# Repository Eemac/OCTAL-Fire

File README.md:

# OCTAL-Fire
The largest collegiate-built drone in the world!
[OCTAL Website!](https://octalfire.com/)

## What/Why is this project?
OCTAL is engineered to respond to wildfires faster--and safer--than humans can. Satellites can already detect hotspots with a resolution of ~500ft. Our system will autonomously deploy to the detected hotspot, perform an analysis with 6 visible and infrared-spectrum cameras, and release retardant before the fire has time to get large, saving wildlife, property, and human lives. With four 66Ah, 60V solid-state LiPo battery packs, a 120kg payload, and a projected 40-minute flight time, OCTAL is built smart, tough, and versatile.

## Commands for power-up on the CANable:
- sudo slcand -f -o -s6 -S 115200 -t hw /dev/ttyACMX can0
- sudo ip link set can0 up
- candump can0
- cansniffer -t 0 can0 (-t 0 will display all messages)
- cansend can0

## CANable Web Flasher:
[Link Here](https://canable.io/updater/canable2.html)

## Directory Structure:
### Root

| Path | Description |
|---|---|
| `Firmware/` | Embedded firmware for flight systems, BMS, charger, and CAN communication. |
| `Hardware/` | KiCad PCB designs, fabrication outputs, and mechanical files. |
| `libraries/` | Shared KiCad symbols, footprints, and 3D models. |
| `Software (Sensing)/` | Placeholder for sensing-side software. |
| `Software (Base Station)/` | Placeholder for base station software. |
| `README.md` | Main project overview. |

---

### Firmware/
Main embedded software tree.

| Path | Description |
|---|---|
| `Core/` | Main flight controller firmware. |
| `BMS/` | Battery Management System firmware. |
| `Charger/` | Charger controller firmware. |
| `can_api/` | Python CAN code-generation tools. |
| `libraries/` | Embedded driver libraries. |
| `can_lib.dbc` | CAN database definitions. |
| `x11.dbc` | Additional CAN message definitions. |
| `requirements.txt` | Python dependencies. |
| `run.sh` | Build script. for CAN message functions |

### Firmware/can_api/

Python tooling for generating CAN interfaces.

| File | Description |
|---|---|
| `c_generator.py` | Generates C CAN interface code. |
| `dbc_generator.py` | Generates DBC files. |
| `yaml_handler.py` | Parses YAML definitions. |
| `utils.py` | Shared helper functions. |
| `tests/` | Unit tests for generators. |
| `files/c_templates/` | Templates for generated C code. |

---

### Hardware/

PCB and electrical hardware designs.

| PCB / Project | Description |
|---|---|
| `Core/flight-core` | Main flight controller and avionics motherboard integrating STM32 control, CAN routing, power conversion, Cube interface logic, and system interconnects. |
| `BMS/` | Battery Management System board handling cell monitoring, balancing, thermistor sensing, fan control, and high-voltage battery telemetry. |
| `Power Board/` | High-current power distribution board for routing battery power to vehicle subsystems and monitoring thermal/load conditions. |
| `PowerFet/` | High-side MOSFET switching board for controllable power distribution and subsystem shutdown protection. |
| `Charger/` | Dedicated battery charger controller board with onboard regulators, USB-C input handling, and programmable charge control circuitry. |
| `GroundRing/` | Ground-distribution PCB intended to centralize system grounding and reduce high-current return path issues. |
| `Cube-Flipper/` | Adapter/interface board for Cube flight controller mounting or signal rerouting. |
| `Power Board/Thermistors/` | Small thermistor sensing daughterboard used for distributed temperature monitoring. |
| `Coaster/` | Small auxiliary/demo PCB project included in the repository. |
---

### libraries/

Shared KiCad libraries.

| Path | Description |
|---|---|
| `3DModels/` | STEP/STP component models. |
| `OlinBAD.pretty/` | Custom PCB footprints. |
| `parts/` | Symbols, footprints, datasheets, and docs. |
| `OlinBAD.kicad_sym` | KiCad symbol library. |

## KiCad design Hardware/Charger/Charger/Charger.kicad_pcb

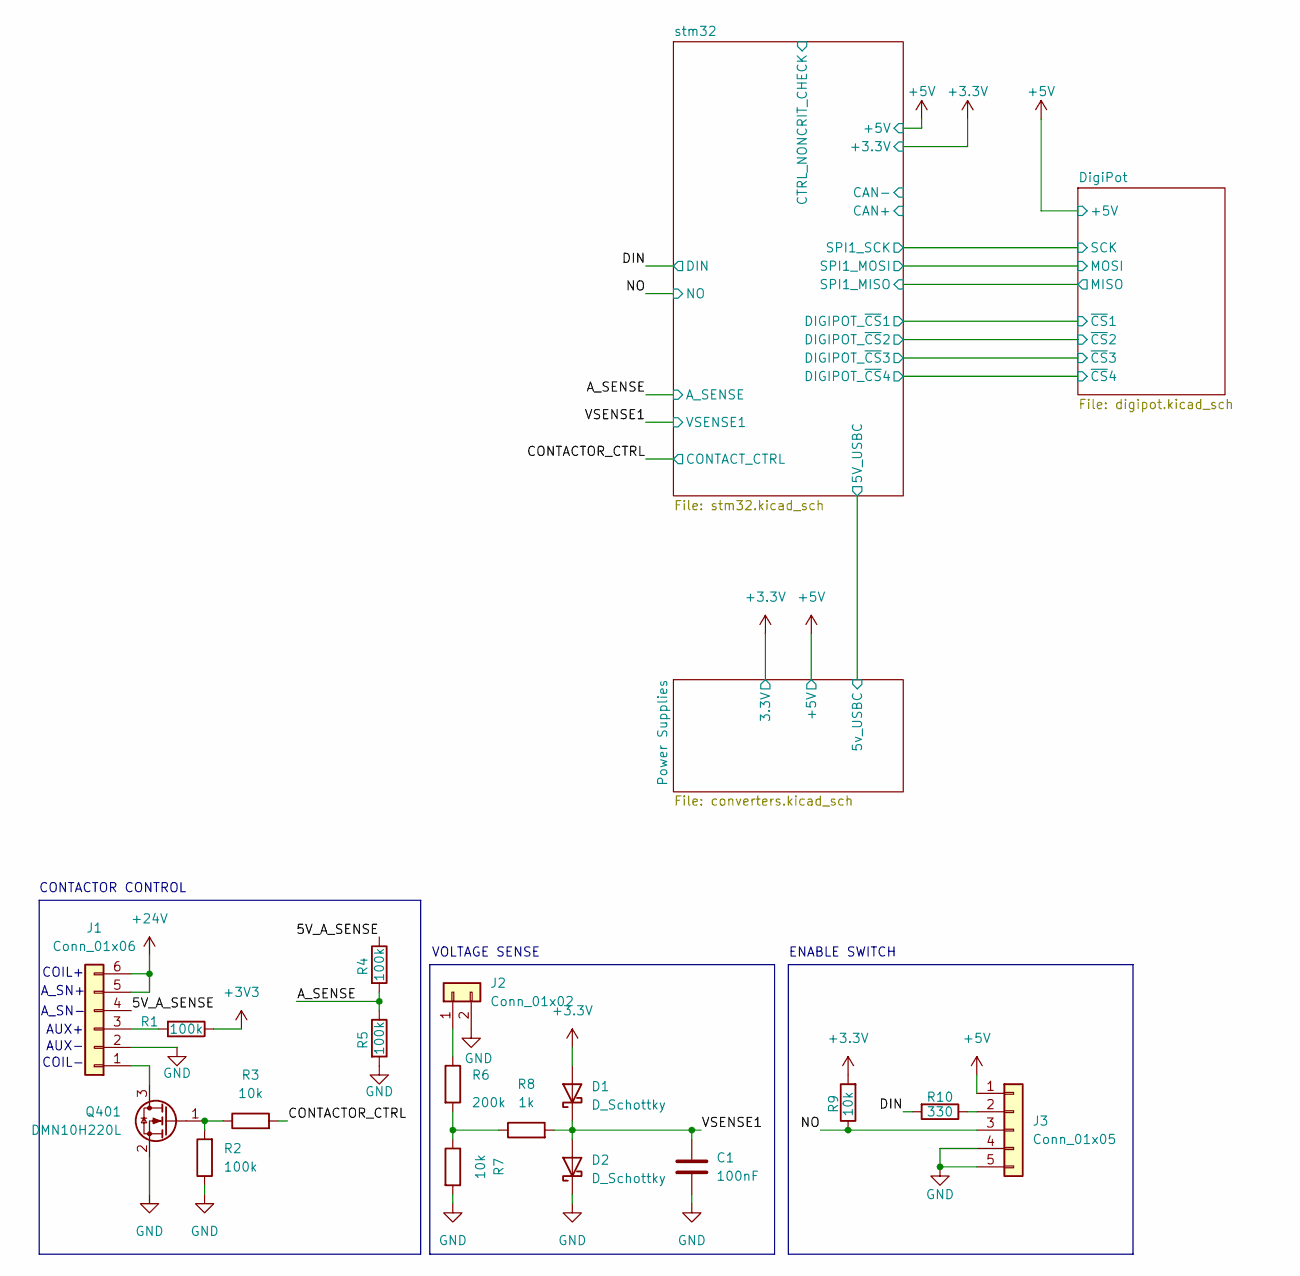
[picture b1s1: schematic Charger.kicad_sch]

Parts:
C1: 100nF; C_0603_1608Metric
D1, D2: D_Schottky; D_0201_0603Metric
J1: Conn_01x06; Molex_Micro-Fit_3.0_43650-0600_1x06_P3.00mm_Horizontal
J2: Conn_01x02; Molex_Micro-Fit_3.0_43650-0200_1x02_P3.00mm_Horizontal
J3: Conn_01x05; Molex_Micro-Fit_3.0_43650-0500_1x05_P3.00mm_Horizontal
Q401: DMN10H220L; SOT-23
R1, R2, R4, R5: 100k; R_0603_1608Metric
R3, R7, R9: 10k; R_0603_1608Metric
R6: 200k; R_0603_1608Metric
R8: 1k; R_0603_1608Metric
R10: 330; R_0603_1608Metric

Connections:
+3.3V: D1.2 (A), R9.2; also elsewhere on the board
+3V3: R1.1
+5V: J3.1; also elsewhere on the board
+24V: J1.5, J1.6; also elsewhere on the board
/5V_A_SENSE: J1.4, R4.1
/A_SENSE: R4.2, R5.1; also elsewhere on the board
/CONTACTOR_CTRL: R3.2; also elsewhere on the board
/DIN: R10.2; also elsewhere on the board
/NO: J3.3, R9.1; also elsewhere on the board
/VSENSE1: C1.1, D1.1 (K), D2.2 (A), R8.2; also elsewhere on the board
GND: C1.2, D2.1 (K), J1.2, J2.2, J3.4, J3.5, Q401.2 (S), R2.1, R5.2, R7.2; also elsewhere on the board
unnamed: J1.1, Q401.3 (D)
unnamed: J1.3, R1.2
unnamed: J2.1, R6.1
unnamed: J3.2, R10.1
unnamed: Q401.1 (G), R2.2, R3.1
unnamed: R6.2, R7.1, R8.1

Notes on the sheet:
COIL+
CONTACTOR CONTROL
COIL-
A_SN+
AUX-
A_SN-
AUX+
VOLTAGE SENSE
ENABLE SWITCH

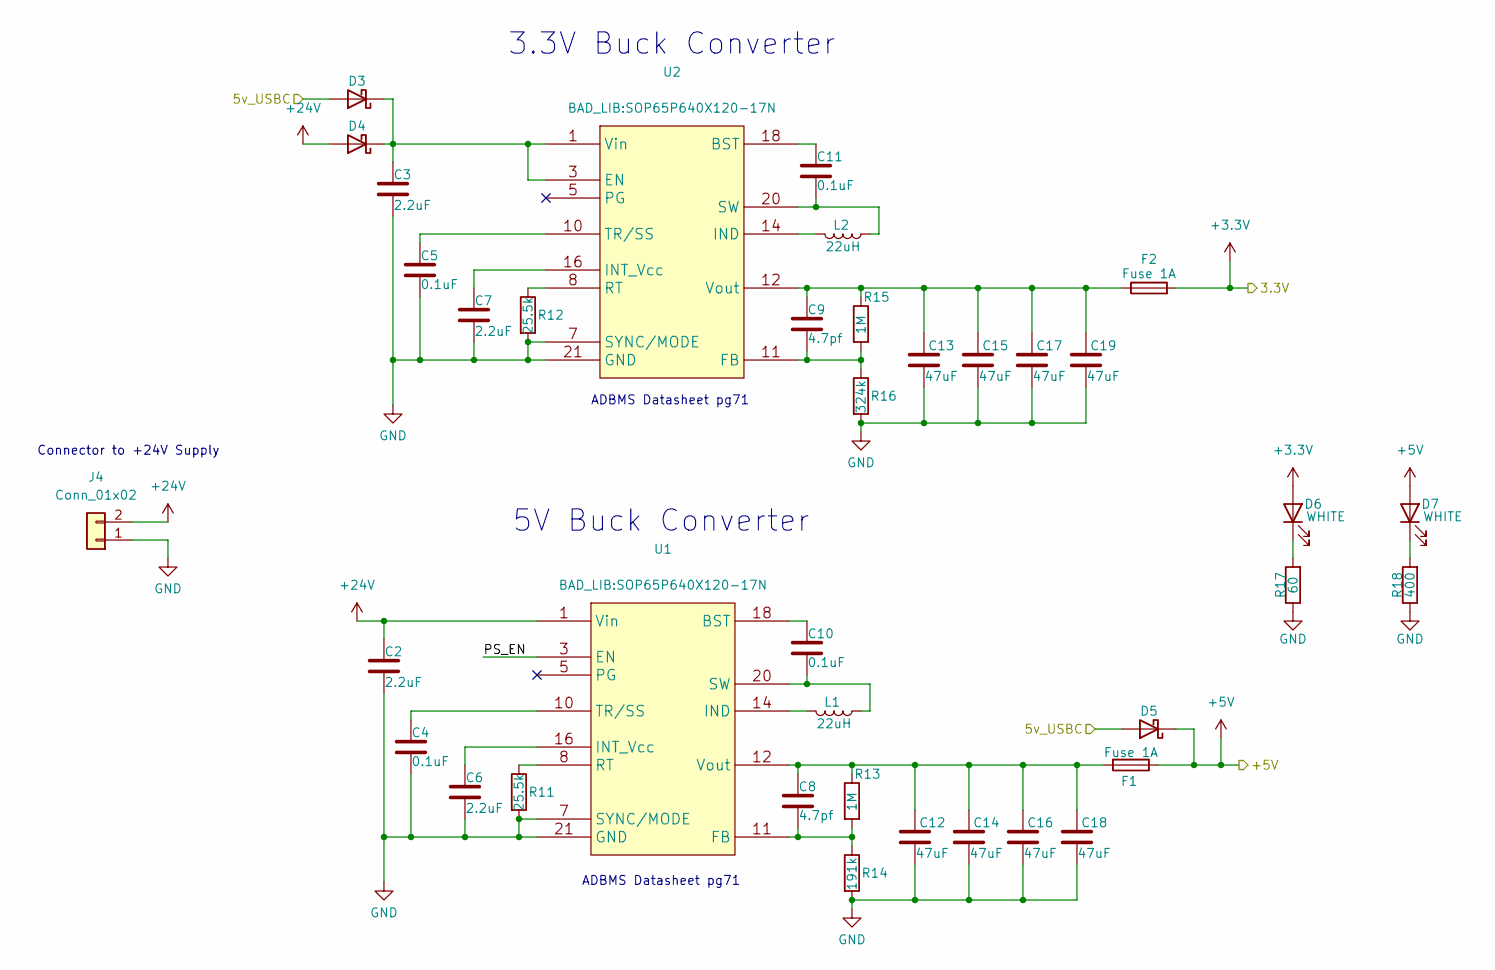
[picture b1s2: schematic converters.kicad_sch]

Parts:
C2, C3: 2.2uF; C_0805_2012Metric
C4, C5, C10, C11: 0.1uF; C_0603_1608Metric
C6, C7: 2.2uF; C_0603_1608Metric
C8, C9: 4.7pf; C_0603_1608Metric
C12, C13, C14, C15, C16, C17, C18, C19: 47uF; C_1206_3216Metric
D3, D4, D5: 60V 3A; DO-220AA_SS2PH10-M3&slash_84A_VIS; MPN V3P6L-M3/H
D6, D7: WHITE; LED_0805_2012Metric
F1, F2: Fuse 1A; Fuse_1206_3216Metric
J4: Conn_01x02; Molex_Micro-Fit_3.0_43650-0200_1x02_P3.00mm_Horizontal
L1, L2: 22uH; L_12x12mm_H4.5mm
R11, R12: 25.5k; R_0603_1608Metric
R13, R15: 1M; R_0603_1608Metric
R14: 191k; R_0603_1608Metric
R16: 324k; R_0603_1608Metric
R17: 60; R_0603_1608Metric
R18: 400; R_0603_1608Metric
U1, U2: SOP65P640X120-17N

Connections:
+3.3V: D6.2 (A), F2.2; also elsewhere on the board
+5V: D5.1 (K), D7.2 (A), F1.1; also elsewhere on the board
+24V: C2.1, D4.2 (A), J4.2, U1.1 (Vin); also elsewhere on the board
/Power Supplies/5v_USBC: D3.2 (A), D5.2 (A); also elsewhere on the board
/Power Supplies/PS_EN: U1.3 (EN)
GND: C2.2, C3.2, C4.2, C5.2, C6.2, C7.2, C12.2, C13.2, C14.2, C15.2, C16.2, C17.2, C18.2, C19.2, J4.1, R11.2, R12.2, R14.2, R16.2, R17.1, R18.1, U1.7 (SYNC/MODE), U1.21 (GND), U2.7 (SYNC/MODE), U2.21 (GND); also elsewhere on the board
unnamed: C3.1, D3.1 (K), D4.1 (K), U2.1 (Vin), U2.3 (EN)
unnamed: D6.1 (K), R17.2
unnamed: D7.1 (K), R18.2
unnamed: C10.1, U1.18 (BST)
unnamed: C8.2, R13.2, R14.1, U1.11 (FB)
unnamed: L1.2, U1.14 (IND)
unnamed: C6.1, U1.16 (INT_Vcc)
unnamed: R11.1, U1.8 (RT)
unnamed: C10.2, L1.1, U1.20 (SW)
unnamed: C4.1, U1.10 (TR/SS)
unnamed: C8.1, C12.1, C14.1, C16.1, C18.1, F1.2, R13.1, U1.12 (Vout)
unnamed: C11.1, U2.18 (BST)
unnamed: C9.2, R15.2, R16.1, U2.11 (FB)
unnamed: L2.2, U2.14 (IND)
unnamed: C7.1, U2.16 (INT_Vcc)
unnamed: R12.1, U2.8 (RT)
unnamed: C11.2, L2.1, U2.20 (SW)
unnamed: C5.1, U2.10 (TR/SS)
unnamed: C9.1, C13.1, C15.1, C17.1, C19.1, F2.1, R15.1, U2.12 (Vout)

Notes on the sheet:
ADBMS Datasheet pg71
5V Buck Converter
Connector to +24V Supply
3.3V Buck Converter

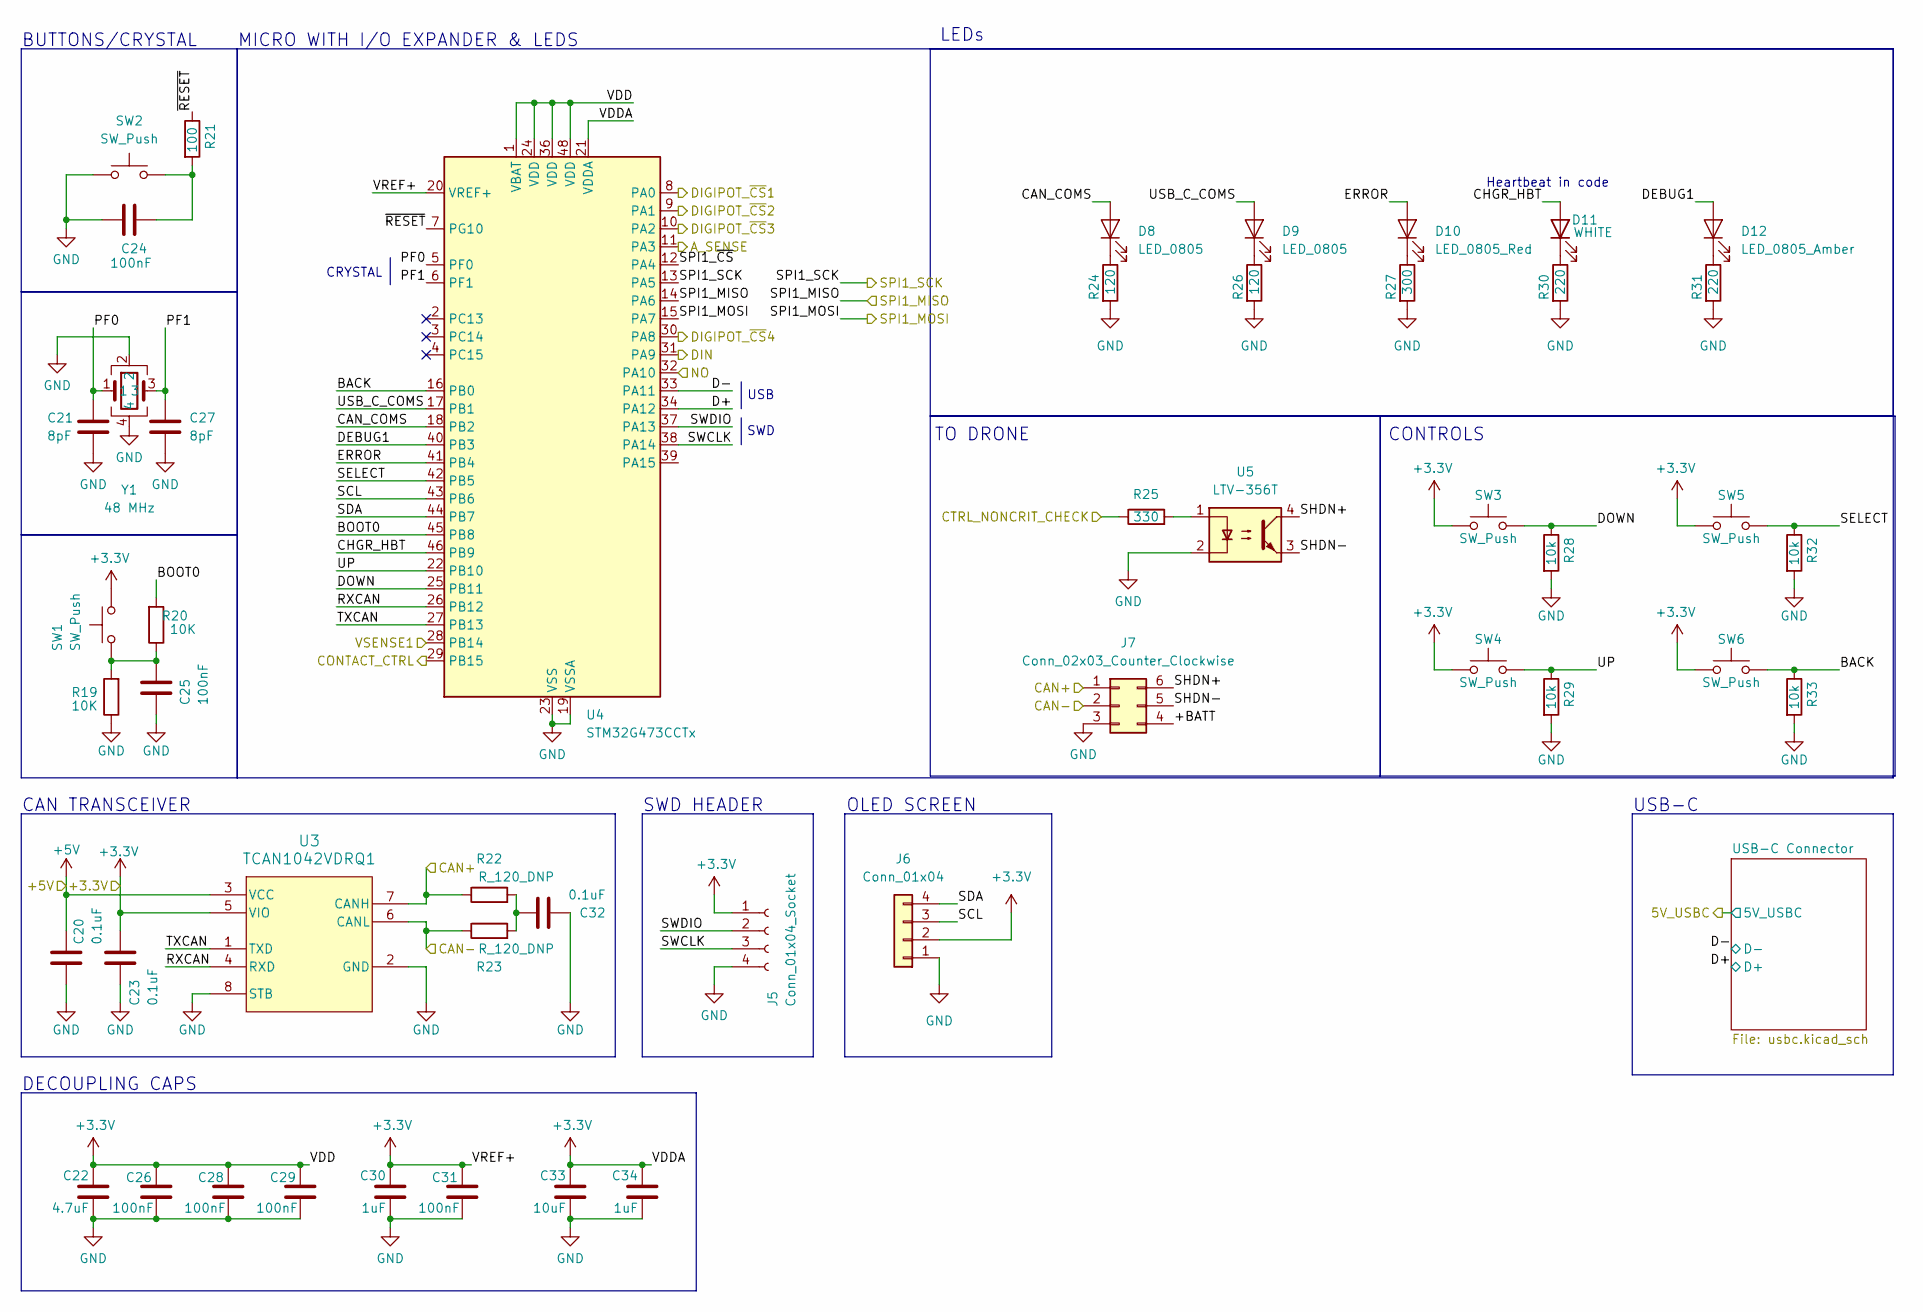
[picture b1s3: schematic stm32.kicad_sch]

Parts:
C20, C23, C32: 0.1uF; C_0603_1608Metric; MPN C0603C104K5RACTU
C21, C27: 8pF; C_0603_1608Metric
C22: 4.7uF; C_0603_1608Metric; MPN 1276-1052-1-ND
C24, C25, C26, C28, C29, C31: 100nF; C_0603_1608Metric; MPN 1276-6717-1-ND
C30, C34: 1uF; C_0603_1608Metric; MPN 1276-1052-1-ND
C33: 10uF; C_0603_1608Metric; MPN 1276-1052-1-ND
D8, D9: LED_0805; LED_0805_2012Metric; MPN 475-1410-1-ND
D10: LED_0805_Red; LED_0805_2012Metric; MPN 475-1415-1-ND
D11: WHITE; LED_0805_2012Metric
D12: LED_0805_Amber; LED_0805_2012Metric; MPN L71517CT-ND
J5: Conn_01x04_Socket; PinSocket_1x04_P2.54mm_Vertical
J6: Conn_01x04; PinHeader_1x04_P2.54mm_Vertical
J7: Conn_02x03_Counter_Clockwise; Molex_Micro-Fit_3.0_43045-0600_2x03_P3.00mm_Horizontal
R19, R20: 10K; R_0603_1608Metric; MPN CRS0805-FX-1002ELFCT-ND
R21: 100; R_0603_1608Metric; MPN CRS0805-FX-1002ELFCT-ND
R22, R23: R_120_DNP; R_0603_1608Metric; MPN 667-ERJ-6ENF1200V
R24, R26: 120; R_0603_1608Metric; MPN 667-ERJ-6ENF1200V
R25: 330; R_0603_1608Metric
R27: 300; R_0603_1608Metric; MPN 667-ERJ-6ENF1200V
R28, R29, R32, R33: 10k; R_0603_1608Metric; MPN CRS0805-FX-1002ELFCT-ND
R30, R31: 220; R_0603_1608Metric; MPN 667-ERJ-6ENF1200V
SW1, SW2, SW3, SW4, SW5, SW6: SW_Push; SW_Push_1P1T_NO_CK_KMR2
U3: TCAN1042VDRQ1; D0008A_M
U4: STM32G473CCTx; LQFP-48_7x7mm_P0.5mm
U5: LTV-356T; SO-4_4.4x3.6mm_P2.54mm
Y1: 48 MHz; Crystal_SMD_SeikoEpson_FA238-4Pin_3.2x2.5mm; MPN 7M48072002

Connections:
+3.3V: C22.1, C23.1, C26.1, C28.1, C29.1, C30.1, C31.1, C33.1, C34.1, J5.1, J6.2, SW1.1, SW3.1, SW4.1, SW5.1, SW6.1, U3.5 (VIO), U4.1 (VBAT), U4.20 (VREF+), U4.21 (VDDA), U4.24 (VDD), U4.36 (VDD), U4.48 (VDD); also elsewhere on the board
+5V: C20.1, U3.3 (VCC); also elsewhere on the board
/A_SENSE: U4.11 (PA3); also elsewhere on the board
/CONTACTOR_CTRL: U4.29 (PB15); also elsewhere on the board
/DIN: U4.31 (PA9); also elsewhere on the board
/DigiPot/~CS1: U4.30 (PA8); also elsewhere on the board
/DigiPot/~CS2: U4.10 (PA2); also elsewhere on the board
/DigiPot/~CS3: U4.9 (PA1); also elsewhere on the board
/DigiPot/~CS4: U4.8 (PA0); also elsewhere on the board
/NO: U4.32 (PA10); also elsewhere on the board
/VSENSE1: U4.28 (PB14); also elsewhere on the board
/stm32/+BATT: J7.4
/stm32/BACK: R33.1, SW6.2, U4.16 (PB0); also elsewhere on the board
/stm32/BOOT0: R20.2, U4.45 (PB8)
/stm32/CAN+: J7.1, R22.1, U3.7 (CANH)
/stm32/CAN-: J7.2, R23.1, U3.6 (CANL)
/stm32/CAN_COMS: D8.2 (A), U4.18 (PB2)
/stm32/CHGR_HBT: D11.2 (A), U4.46 (PB9)
/stm32/CTRL_NONCRIT_CHECK: R25.1, U4.39 (PA15)
/stm32/D+: U4.34 (PA12); also elsewhere on the board
/stm32/D-: U4.33 (PA11); also elsewhere on the board
/stm32/DEBUG1: D12.2 (A), U4.40 (PB3)
/stm32/DOWN: R28.1, SW3.2, U4.25 (PB11); also elsewhere on the board
/stm32/ERROR: D10.2 (A), U4.41 (PB4)
/stm32/PF0: C21.1, U4.5 (PF0), Y1.1
/stm32/PF1: C27.1, U4.6 (PF1), Y1.3
/stm32/RXCAN: U3.4 (RXD), U4.26 (PB12)
/stm32/SCL: J6.3, U4.43 (PB6); also elsewhere on the board
/stm32/SDA: J6.4, U4.44 (PB7); also elsewhere on the board
/stm32/SELECT: R32.1, SW5.2, U4.42 (PB5); also elsewhere on the board
/stm32/SHDN+: J7.6, U5.4
/stm32/SHDN-: J7.5, U5.3
/stm32/SPI1_MISO_L: U4.14 (PA6); also elsewhere on the board
/stm32/SPI1_MOSI: U4.15 (PA7); also elsewhere on the board
/stm32/SPI1_SCK: U4.13 (PA5); also elsewhere on the board
/stm32/SPI1_~CS: U4.12 (PA4)
/stm32/SWCLK: J5.3, U4.38 (PA14)
/stm32/SWDIO: J5.2, U4.37 (PA13)
/stm32/TXCAN: U3.1 (TXD), U4.27 (PB13)
/stm32/UP: R29.1, SW4.2, U4.22 (PB10); also elsewhere on the board
/stm32/USB_C_COMS: D9.2 (A), U4.17 (PB1)
/stm32/~RESET: R21.1, U4.7 (PG10)
GND: C20.2, C21.2, C22.2, C23.2, C24.1, C25.2, C26.2, C27.2, C28.2, C29.2, C30.2, C31.2, C32.2, C33.2, C34.2, J5.4, J6.1, J7.3, R19.1, R24.2, R26.2, R27.2, R28.2, R29.2, R30.2, R31.2, R32.2, R33.2, SW2.1, U3.2 (GND), U3.8 (STB), U4.19 (VSSA), U4.23 (VSS), U4.35 (VSS), U4.47 (VSS), U5.2, Y1.2, Y1.4; also elsewhere on the board
unnamed: C24.2, R21.2, SW2.2
unnamed: C25.1, R19.2, R20.1, SW1.2
unnamed: C32.1, R22.2, R23.2
unnamed: D8.1 (K), R24.1
unnamed: D9.1 (K), R26.1
unnamed: D10.1 (K), R27.1
unnamed: D11.1 (K), R30.1
unnamed: D12.1 (K), R31.1
unnamed: R25.2, U5.1

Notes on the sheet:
Heartbeat in code
CRYSTAL
SWD HEADER
MICRO WITH I/O EXPANDER & LEDS
DECOUPLING CAPS
OLED SCREEN
LEDs
CONTROLS
BUTTONS/CRYSTAL
USB
TO DRONE
USB-C
CAN TRANSCEIVER
SWD

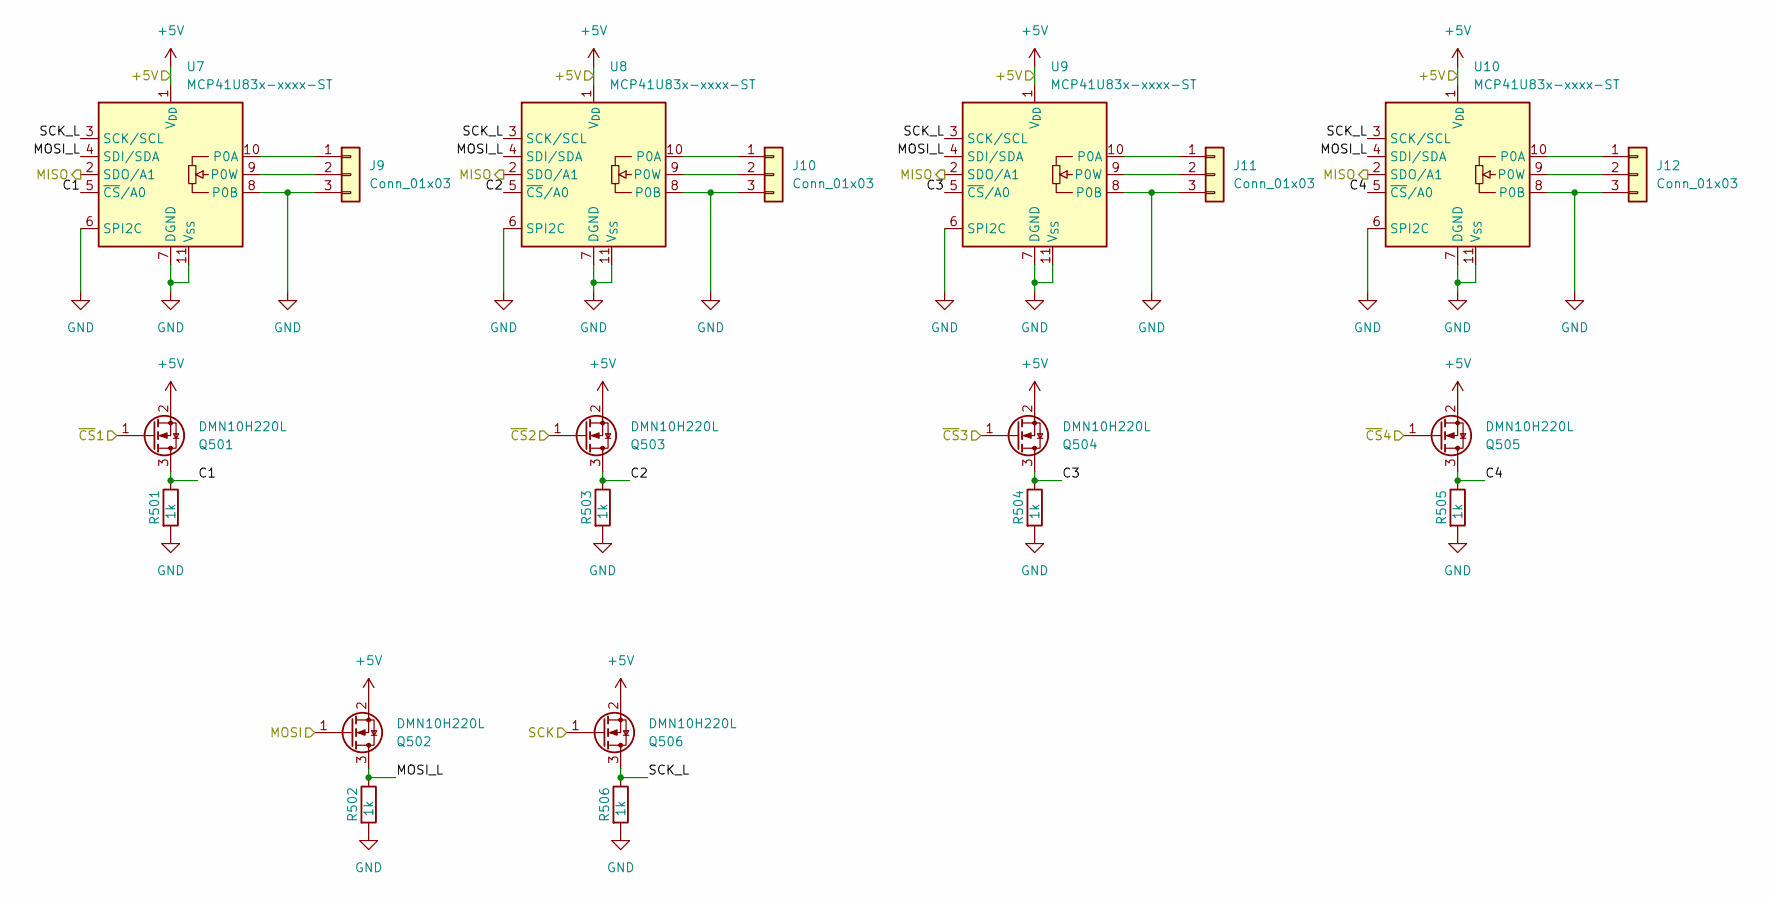
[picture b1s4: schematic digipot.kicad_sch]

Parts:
J9, J10, J11, J12: Conn_01x03; Molex_Micro-Fit_3.0_43650-0300_1x03_P3.00mm_Horizontal
Q501, Q502, Q503, Q504, Q505, Q506: DMN10H220L; SOT-23
R501, R502, R503, R504, R505, R506: 1k; R_0603_1608Metric; MPN 667-ERJ-6ENF1200V
U7, U8, U9, U10: MCP41U83x-xxxx-ST; TSSOP-14_4.4x5mm_P0.65mm

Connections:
+5V: Q501.2 (S), Q502.2 (S), Q503.2 (S), Q504.2 (S), Q505.2 (S), Q506.2 (S), U7.1 (V_{DD}), U8.1 (V_{DD}), U9.1 (V_{DD}), U10.1 (V_{DD}); also elsewhere on the board
/DigiPot/C1: Q501.3 (D), R501.1, U7.5 (~CS/A0)
/DigiPot/C2: Q503.3 (D), R503.1, U8.5 (~CS/A0)
/DigiPot/C3: Q504.3 (D), R504.1, U9.5 (~CS/A0)
/DigiPot/C4: Q505.3 (D), R505.1, U10.5 (~CS/A0)
/DigiPot/MISO: U7.2 (SDO/A1), U8.2 (SDO/A1), U9.2 (SDO/A1), U10.2 (SDO/A1); also elsewhere on the board
/DigiPot/MOSI_L: Q502.3 (D), R502.1, U7.4 (SDI/SDA), U8.4 (SDI/SDA), U9.4 (SDI/SDA), U10.4 (SDI/SDA)
/DigiPot/SCK_L: Q506.3 (D), R506.1, U7.3 (SCK/SCL), U8.3 (SCK/SCL), U9.3 (SCK/SCL), U10.3 (SCK/SCL)
/DigiPot/~CS1: Q501.1 (G); also elsewhere on the board
/DigiPot/~CS2: Q503.1 (G); also elsewhere on the board
/DigiPot/~CS3: Q504.1 (G); also elsewhere on the board
/DigiPot/~CS4: Q505.1 (G); also elsewhere on the board
/stm32/SPI1_MOSI: Q502.1 (G); also elsewhere on the board
/stm32/SPI1_SCK: Q506.1 (G); also elsewhere on the board
GND: J9.3, J10.3, J11.3, J12.3, R501.2, R502.2, R503.2, R504.2, R505.2, R506.2, U7.6 (SPI2C), U7.7 (DGND), U7.8 (P0B), U7.11 (V_{SS}), U8.6 (SPI2C), U8.7 (DGND), U8.8 (P0B), U8.11 (V_{SS}), U9.6 (SPI2C), U9.7 (DGND), U9.8 (P0B), U9.11 (V_{SS}), U10.6 (SPI2C), U10.7 (DGND), U10.8 (P0B), U10.11 (V_{SS}); also elsewhere on the board
unnamed: J9.1, U7.10 (P0A)
unnamed: J9.2, U7.9 (P0W)
unnamed: J10.1, U8.10 (P0A)
unnamed: J10.2, U8.9 (P0W)
unnamed: J11.1, U9.10 (P0A)
unnamed: J11.2, U9.9 (P0W)
unnamed: J12.1, U10.10 (P0A)
unnamed: J12.2, U10.9 (P0W)

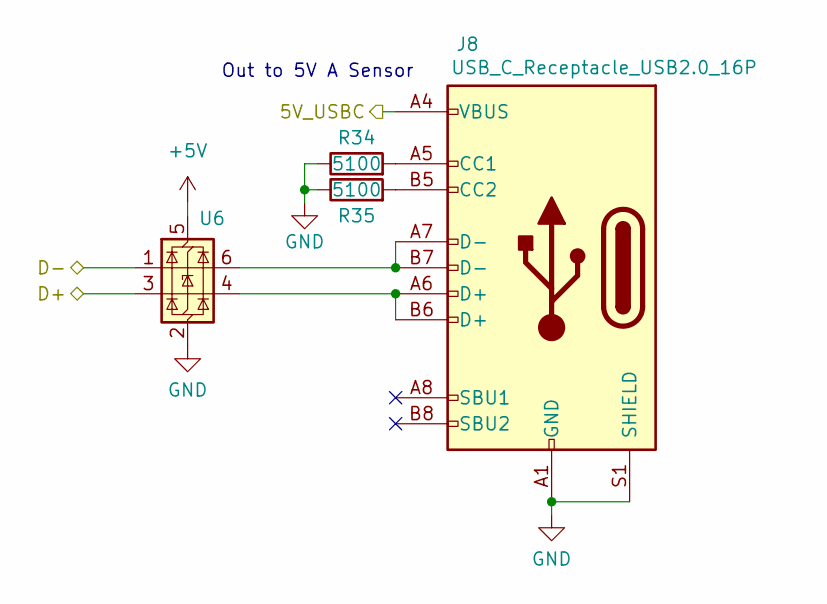
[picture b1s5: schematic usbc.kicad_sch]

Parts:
J8: USB_C_Receptacle_USB2.0_16P; USB_C_Receptacle_GCT_USB4105-xx-A_16P_TopMnt_Horizontal
R34, R35: 5100; R_0603_1608Metric
U6: USBLC6-2SC6; SOT-23-6

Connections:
+5V: U6.5 (VBUS); also elsewhere on the board
/Power Supplies/5v_USBC: J8.A4 (VBUS), J8.A9 (VBUS), J8.B4 (VBUS), J8.B9 (VBUS); also elsewhere on the board
/stm32/D+: U6.3 (I/O2); also elsewhere on the board
/stm32/D-: U6.1 (I/O1); also elsewhere on the board
GND: J8.A1 (GND), J8.A12 (GND), J8.B1 (GND), J8.B12 (GND), J8.S1 (SHIELD), R34.1, R35.1, U6.2 (GND); also elsewhere on the board
unnamed: J8.A5 (CC1), R34.2
unnamed: J8.B5 (CC2), R35.2
unnamed: J8.A6 (D+), J8.B6 (D+), U6.4 (I/O2)
unnamed: J8.A7 (D-), J8.B7 (D-), U6.6 (I/O1)

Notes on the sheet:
Out to 5V A Sensor

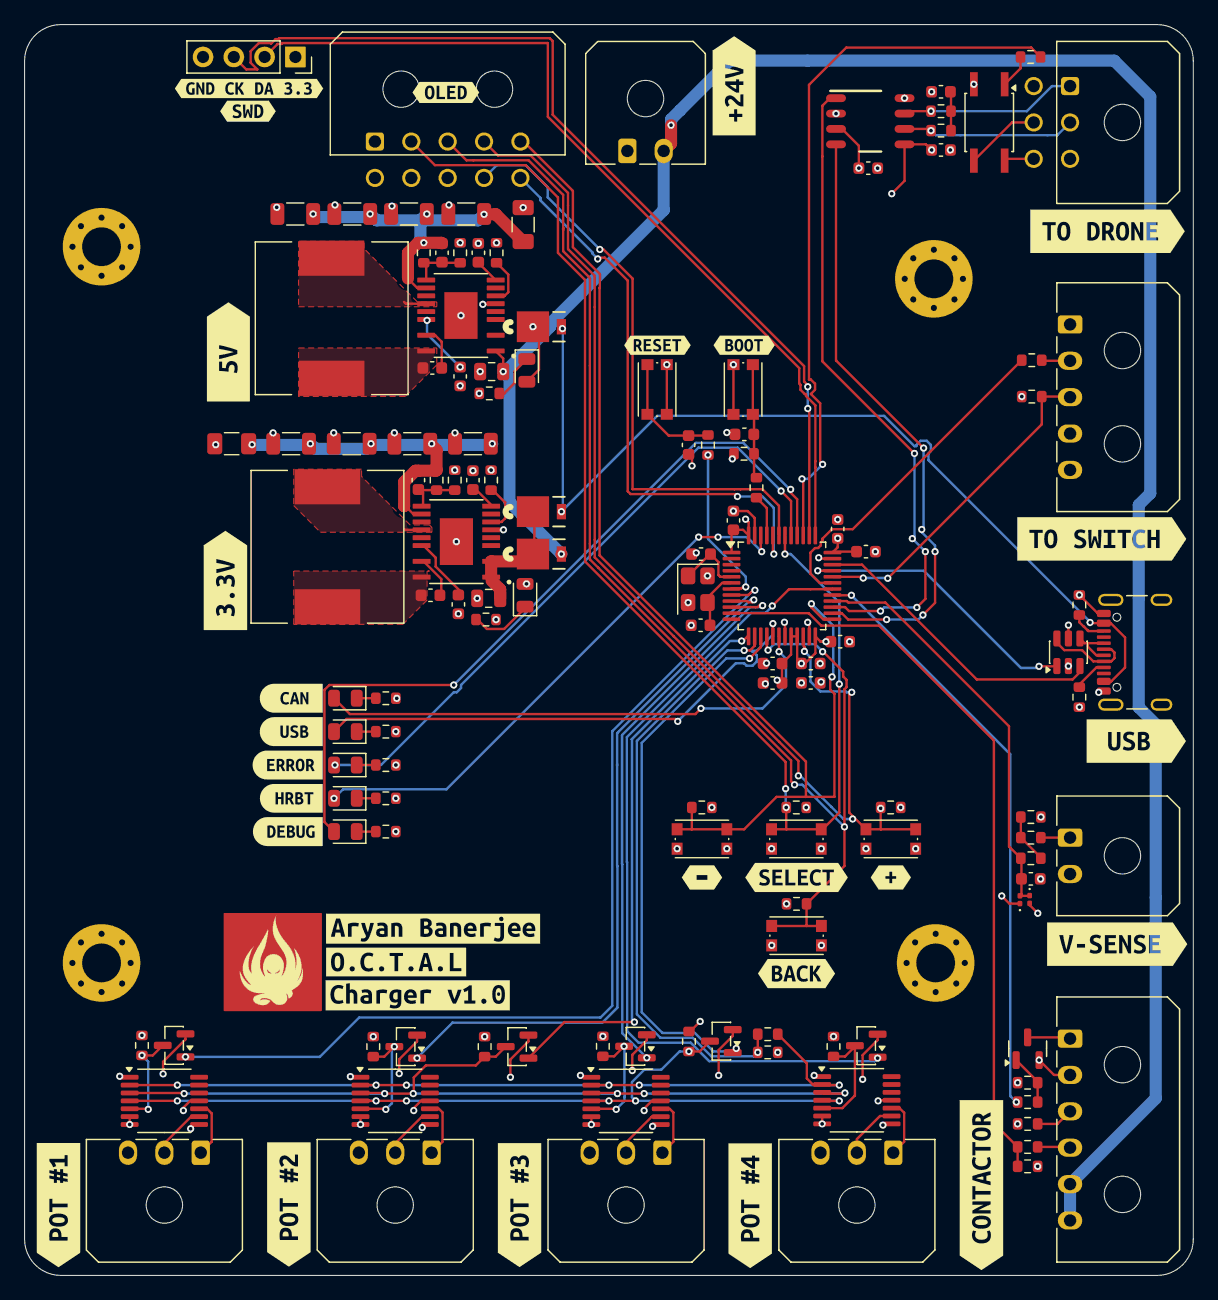
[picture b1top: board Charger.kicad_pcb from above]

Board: 4 copper layers, 96.4 x 103.2 mm, 162 parts (0 on the bottom side), 97 nets.

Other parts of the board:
H301, H302, H303, H304: MountingHole_Pad; MountingHole_3.2mm_M3_Pad_Via
J301: Conn_02x05_Counter_Clockwise; Molex_Micro-Fit_3.0_43045-1000_2x05_P3.00mm_Horizontal
R301: 1k; R_0603_1608Metric
R302: 2.2k; R_0603_1608Metric
kibuzzard-69B34D34: G***; kibuzzard-69B34D34
kibuzzard-69B34D41: G***; kibuzzard-69B34D41
kibuzzard-69B34DA5: G***; kibuzzard-69B34DA5
kibuzzard-69B34DB2: G***; kibuzzard-69B34DB2
kibuzzard-69B34DBF: G***; kibuzzard-69B34DBF
kibuzzard-69B34DC8: G***; kibuzzard-69B34DC8
kibuzzard-69B34E6D: G***; kibuzzard-69B34E6D
kibuzzard-69B34E29: G***; kibuzzard-69B34E29
kibuzzard-69B34E60: G***; kibuzzard-69B34E60
kibuzzard-69B36C6C: G***; kibuzzard-69B36C6C
kibuzzard-69B36C7B: G***; kibuzzard-69B36C7B
kibuzzard-69B36C96: G***; kibuzzard-69B36C96
kibuzzard-69B36CA5: G***; kibuzzard-69B36CA5
kibuzzard-69B36CC2: G***; kibuzzard-69B36CC2
kibuzzard-69B81BEB: G***; kibuzzard-69B81BEB
kibuzzard-69B81C0B: G***; kibuzzard-69B81C0B
kibuzzard-69B81D82: G***; kibuzzard-69B81D82
kibuzzard-69B81DBD: G***; kibuzzard-69B81DBD
kibuzzard-69B81DEB: G***; kibuzzard-69B81DEB
kibuzzard-69B81E61: G***; kibuzzard-69B81E61
kibuzzard-69B81E77: G***; kibuzzard-69B81E77
kibuzzard-69B821F4: G***; kibuzzard-69B821F4
kibuzzard-69B824A2: G***; kibuzzard-69B824A2
kibuzzard-69B8247B: G***; kibuzzard-69B8247B
kibuzzard-69B82222: G***; kibuzzard-69B82222
kibuzzard-69B82233: G***; kibuzzard-69B82233
kibuzzard-69B82281: G***; kibuzzard-69B82281
kibuzzard-690FB70C: G***; kibuzzard-690FB70C
kibuzzard-690FB638: G***; kibuzzard-690FB638

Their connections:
+3.3V: J301.1, J301.8; also elsewhere on the board
/DigiPot/MISO: R301.1; also elsewhere on the board
/stm32/BACK: J301.3; also elsewhere on the board
/stm32/DOWN: J301.5; also elsewhere on the board
/stm32/SCL: J301.9; also elsewhere on the board
/stm32/SDA: J301.10; also elsewhere on the board
/stm32/SELECT: J301.2; also elsewhere on the board
/stm32/SPI1_MISO_L: R301.2, R302.1; also elsewhere on the board
/stm32/UP: J301.4; also elsewhere on the board
GND: H301.1, H302.1, H303.1, H304.1, J301.7, R302.2; also elsewhere on the board

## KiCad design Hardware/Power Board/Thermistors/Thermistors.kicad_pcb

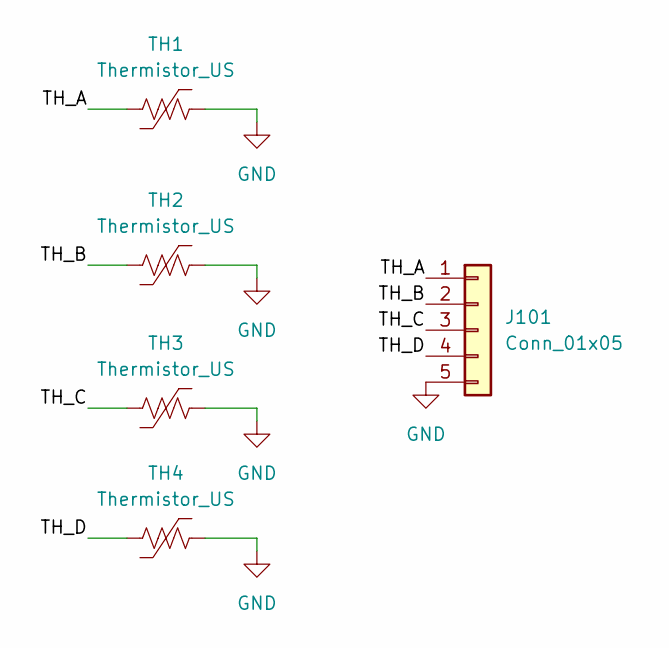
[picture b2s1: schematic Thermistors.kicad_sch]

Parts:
J101: Conn_01x05; FPC_5pin
TH1, TH2, TH3, TH4: Thermistor_US; R_0402_1005Metric

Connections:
/TH_A: J101.1, TH1.1
/TH_B: J101.2, TH2.1
/TH_C: J101.3, TH3.1
/TH_D: J101.4, TH4.1
GND: J101.5, TH1.2, TH2.2, TH3.2, TH4.2

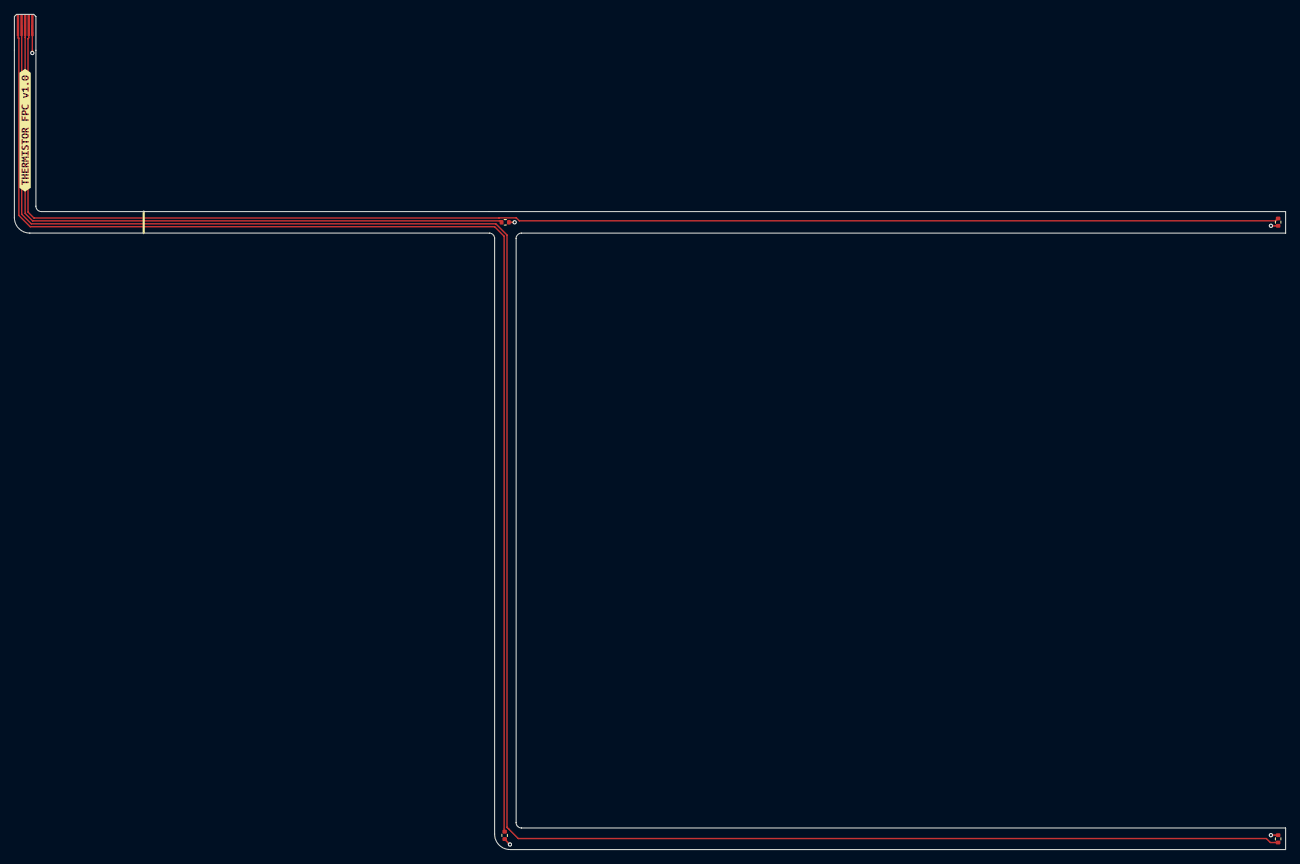
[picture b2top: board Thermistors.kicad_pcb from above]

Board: 2 copper layers, 177.1 x 116.4 mm, 6 parts (0 on the bottom side), 5 nets.

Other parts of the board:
kibuzzard-6936739F: G***; kibuzzard-6936739F

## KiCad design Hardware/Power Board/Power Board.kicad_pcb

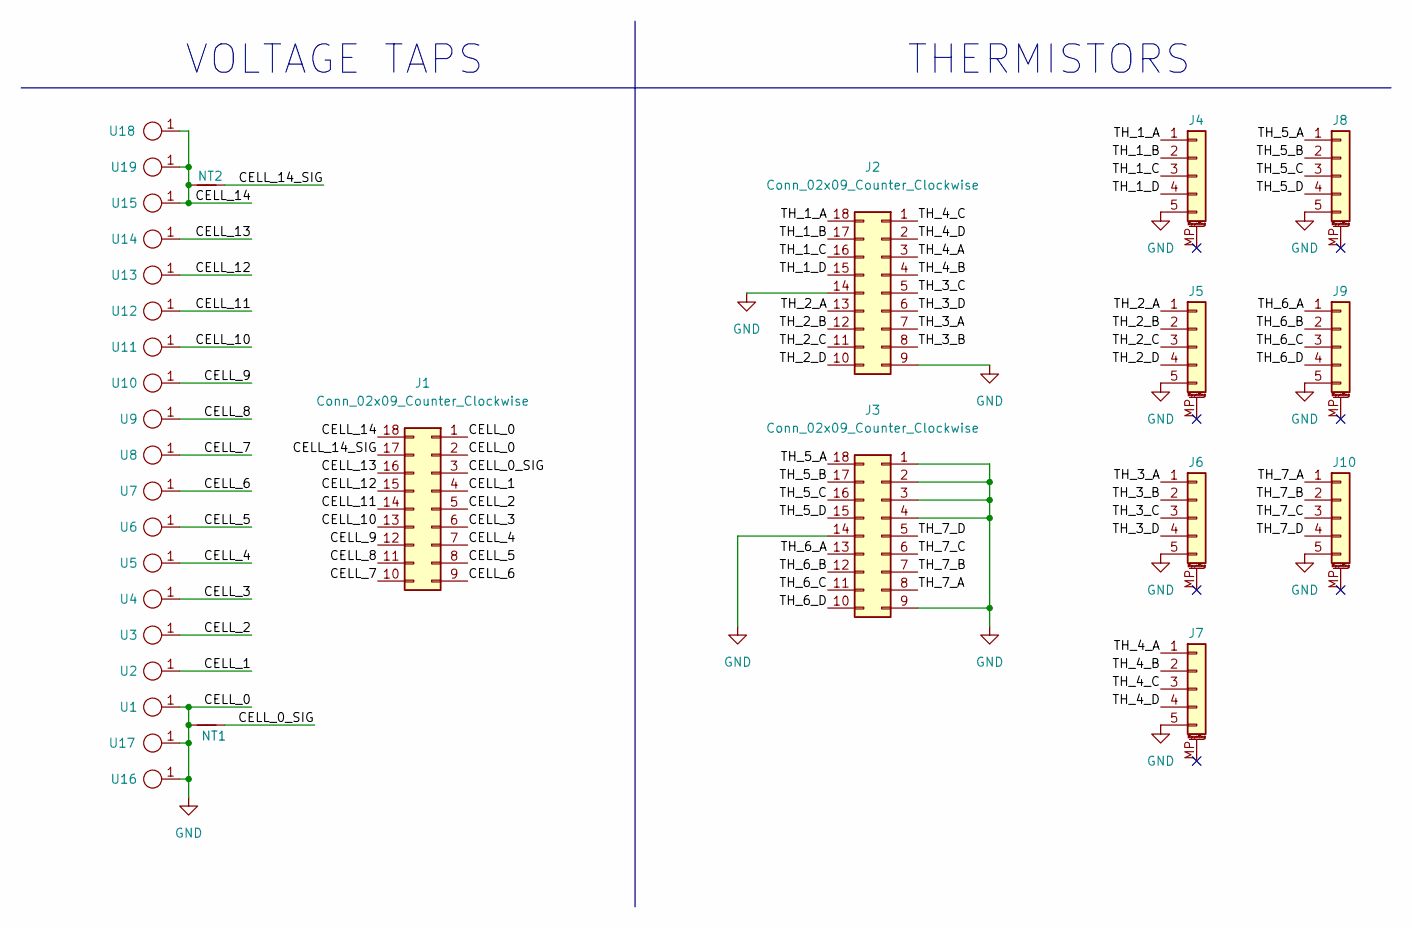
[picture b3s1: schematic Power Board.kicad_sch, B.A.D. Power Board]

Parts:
J1, J2, J3: Conn_02x09_Counter_Clockwise; PinHeader_2x09_P2.54mm_Vertical
J4, J5, J6, J7, J8, J9, J10: Conn_01x05_MountingPin; TE_0-1734839-5_1x05-1MP_P0.5mm_Horizontal
NT1, NT2: NetTie_2; NetTie-2_SMD_Pad0.5mm
U1, U2, U3, U4, U5, U6, U7, U8, U9, U10, U11, U12, U13, U14, U15: BatteryTab
U16, U17, U18, U19: 7461098

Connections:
/CELL_0_SIG: J1.3, NT1.2
/CELL_1: J1.4, U2.1
/CELL_2: J1.5, U3.1
/CELL_3: J1.6, U4.1
/CELL_4: J1.7, U5.1
/CELL_5: J1.8, U6.1
/CELL_6: J1.9, U7.1
/CELL_7: J1.10, U8.1
/CELL_8: J1.11, U9.1
/CELL_9: J1.12, U10.1
/CELL_10: J1.13, U11.1
/CELL_11: J1.14, U12.1
/CELL_12: J1.15, U13.1
/CELL_13: J1.16, U14.1
/CELL_14: J1.18, NT2.2, U15.1, U18.1, U19.1
/CELL_14_SIG: J1.17, NT2.1
/TH_1_A: J2.18, J4.1
/TH_1_B: J2.17, J4.2
/TH_1_C: J2.16, J4.3
/TH_1_D: J2.15, J4.4
/TH_2_A: J2.13, J5.1
/TH_2_B: J2.12, J5.2
/TH_2_C: J2.11, J5.3
/TH_2_D: J2.10, J5.4
/TH_3_A: J2.7, J6.1
/TH_3_B: J2.8, J6.2
/TH_3_C: J2.5, J6.3
/TH_3_D: J2.6, J6.4
/TH_4_A: J2.3, J7.1
/TH_4_B: J2.4, J7.2
/TH_4_C: J2.1, J7.3
/TH_4_D: J2.2, J7.4
/TH_5_A: J3.18, J8.1
/TH_5_B: J3.17, J8.2
/TH_5_C: J3.16, J8.3
/TH_5_D: J3.15, J8.4
/TH_6_A: J3.13, J9.1
/TH_6_B: J3.12, J9.2
/TH_6_C: J3.11, J9.3
/TH_6_D: J3.10, J9.4
/TH_7_A: J3.8, J10.1
/TH_7_B: J3.7, J10.2
/TH_7_C: J3.6, J10.3
/TH_7_D: J3.5, J10.4
GND: J1.1, J1.2, J2.9, J2.14, J3.1, J3.2, J3.3, J3.4, J3.9, J3.14, J4.5, J5.5, J6.5, J7.5, J8.5, J9.5, J10.5, NT1.1, U1.1, U16.1, U17.1

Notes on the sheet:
THERMISTORS
VOLTAGE TAPS

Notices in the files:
Firmware/BMS/can_lib.h:
@copyright Copyright (c) 2018-2019 Erik Moqvist
The MIT License (MIT)
